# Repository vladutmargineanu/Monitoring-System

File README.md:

# Monitoring-System
Monitoring system with accelerometer, temperature sensor and light sensor - Project for the Computer Engineering course @ ACS, UPB 2020

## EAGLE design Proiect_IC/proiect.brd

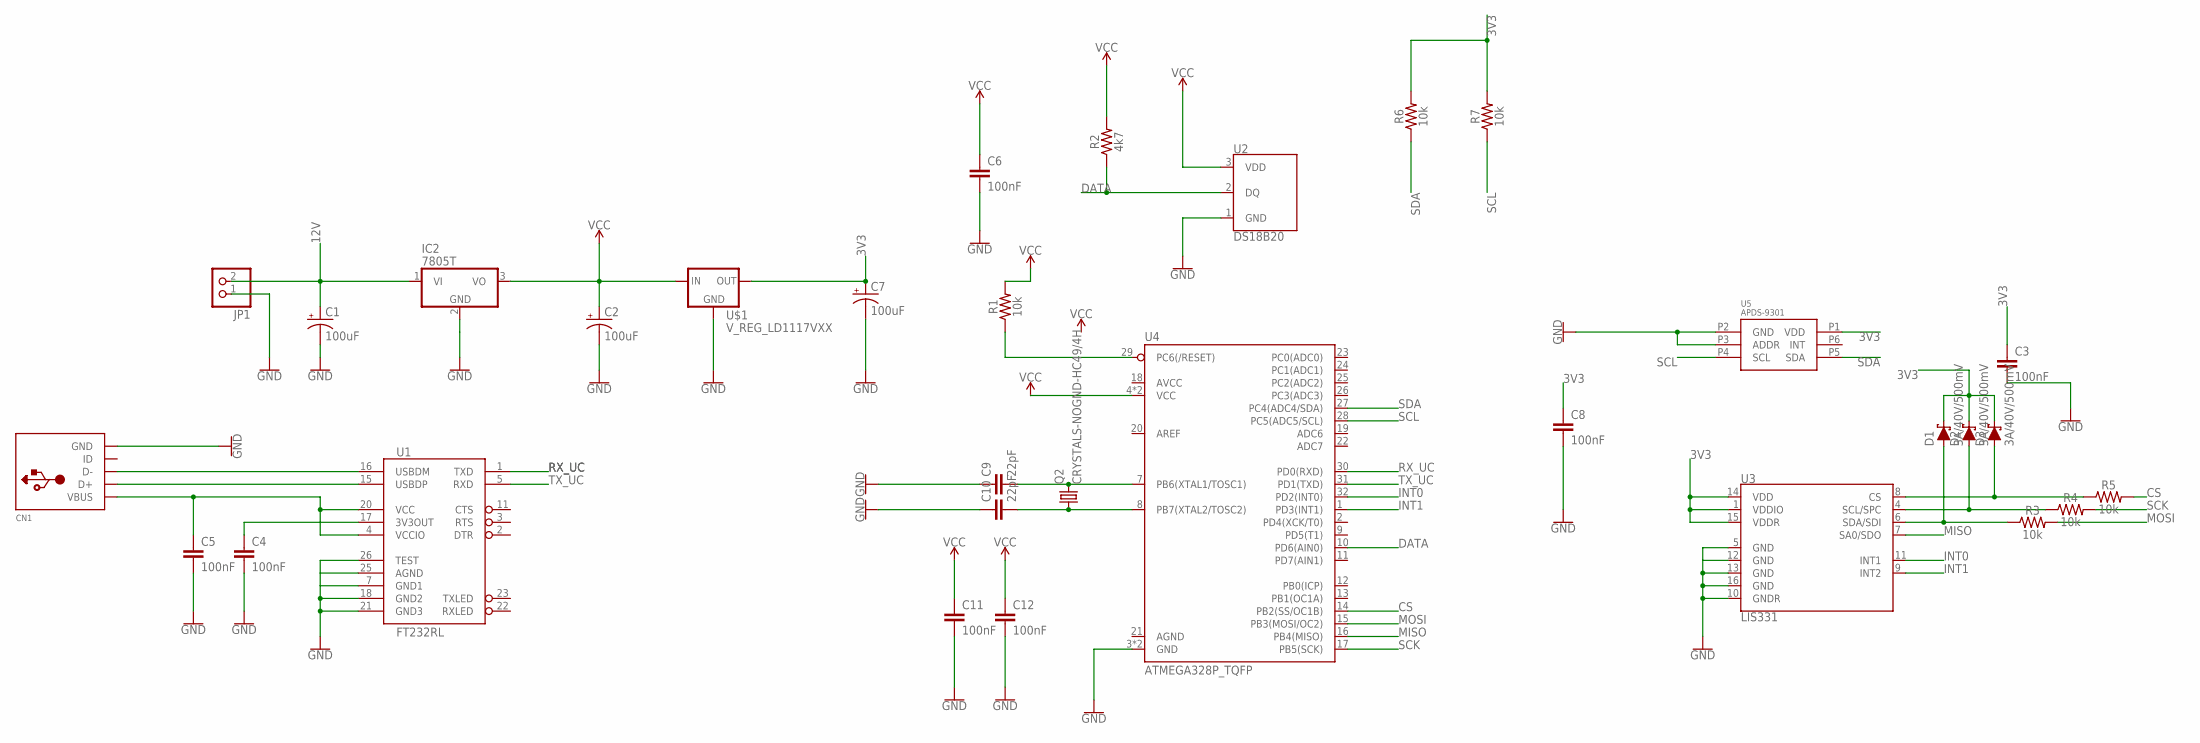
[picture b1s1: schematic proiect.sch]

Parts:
C1, C2, C7: 100uF; CPOL-RADIAL-2.5MM-6.5MM
C3, C4, C5, C6, C8, C11, C12: 100nF; 0603
C9, C10: 22pF; 0603
CN1: USBMINIB; USB-MINIB
D1, D2, D3: 3A/40V/500mV; SMA-DIODE
IC2: 7805T; TO220H
JP1: PINHD-1X2; 1X02
Q2: CRYSTALS-NOGND-HC49/4H; HC49
R1, R3, R4, R5, R6, R7: 10k; 0603
R2: 4k7; 0603
U1: FT232RL; SSOP28DB
U2: DS18B20; TO-92-AMMO
U3: LIS331; LGA-16-3X3
U4: ATMEGA328P_TQFP; TQFP32-08
U5: APDS-9301; CHIPLED-6
U$1: V_REG_LD1117VXX; 78XXL

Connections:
3V3: C3.1, C7.1 (+), C8.1, D1.C, D2.C, D3.C, R6.2, R7.2, U3.1 (VDDIO), U3.14 (VDD), U3.15 (VDDR), U5.P1 (VDD), U$1.GND (OUT)
12V: C1.1 (+), IC2.1 (VI), JP1.2
CS: R5.2, U4.14 (PB2(SS/OC1B))
DATA: R2.1, U2.2 (DQ), U4.10 (PD6(AIN0))
GND: C1.2 (-), C2.2 (-), C3.2, C4.2, C5.2, C6.2, C7.2 (-), C8.2, C9.1, C10.1, C11.2, C12.2, CN1.GND, IC2.2 (GND), JP1.1, U1.7 (GND1), U1.18 (GND2), U1.21 (GND3), U1.25 (AGND), U1.26 (TEST), U2.1 (GND), U3.5 (GND), U3.10 (GNDR), U3.12 (GND), U3.13 (GND), U3.16 (GND), U4.3 (GND), U4.5 (GND), U5.P2 (GND), U5.P3 (ADDR), U$1.IN (GND)
INT0: U3.11 (INT1), U4.32 (PD2(INT0))
INT1: U3.9 (INT2), U4.1 (PD3(INT1))
MISO: U3.7 (SA0/SDO), U4.16 (PB4(MISO))
MOSI: R3.2, U4.15 (PB3(MOSI/OC2))
unnamed: CN1.D-, U1.16 (USBDM)
unnamed: CN1.D+, U1.15 (USBDP)
unnamed: C5.1, CN1.VBUS, U1.4 (VCCIO), U1.20 (VCC)
unnamed: C4.1, U1.17 (3V3OUT)
unnamed: C9.2, Q2.2, U4.7 (PB6(XTAL1/TOSC1))
unnamed: C10.2, Q2.1, U4.8 (PB7(XTAL2/TOSC2))
unnamed: R1.1, U4.29 (PC6(/RESET))
unnamed: D1.A, R3.1, U3.6 (SDA/SDI)
unnamed: D2.A, R4.1, U3.4 (SCL/SPC)
unnamed: D3.A, R5.1, U3.8 (CS)
RX_UC: U1.1 (TXD), U4.30 (PD0(RXD))
SCK: R4.2, U4.17 (PB5(SCK))
SCL: R7.1, U4.28 (PC5(ADC5/SCL)), U5.P4 (SCL)
SDA: R6.1, U4.27 (PC4(ADC4/SDA)), U5.P5 (SDA)
TX_UC: U1.5 (RXD), U4.31 (PD1(TXD))
VCC: C2.1 (+), C6.1, C11.1, C12.1, IC2.3 (VO), R1.2, R2.2, U2.3 (VDD), U4.4 (VCC), U4.6 (VCC), U$1.OUT (IN)

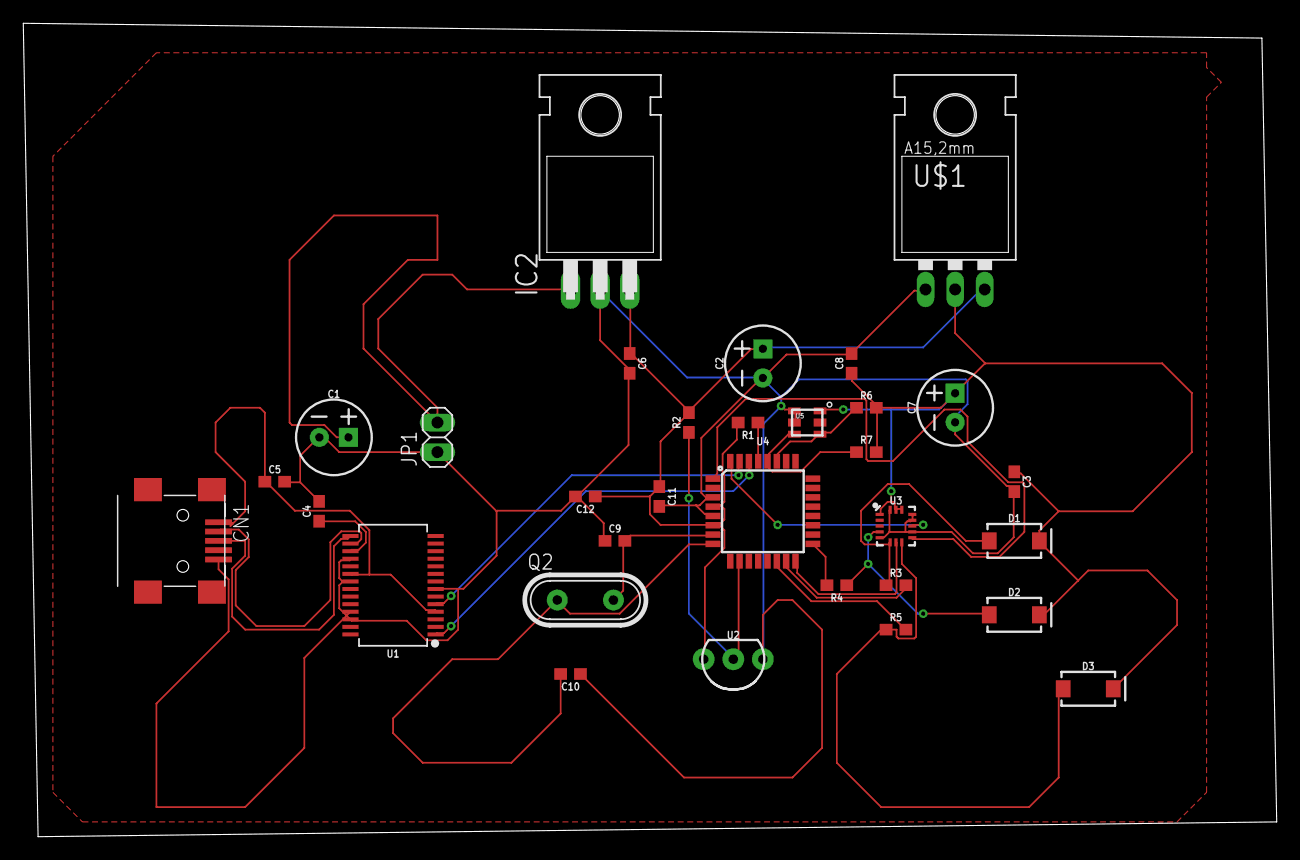
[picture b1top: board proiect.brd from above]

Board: 2 copper layers, 107.6 x 69.8 mm, 32 parts (0 on the bottom side), 25 nets.

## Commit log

2020-05-07 Enunt
2020-05-07 Final Work

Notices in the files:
parts and their libraries:
SparkFun-Capacitors: Licensing: Creative Commons ShareAlike 4.0 International - https://creativecommons.org/licenses/by-sa/4.0
